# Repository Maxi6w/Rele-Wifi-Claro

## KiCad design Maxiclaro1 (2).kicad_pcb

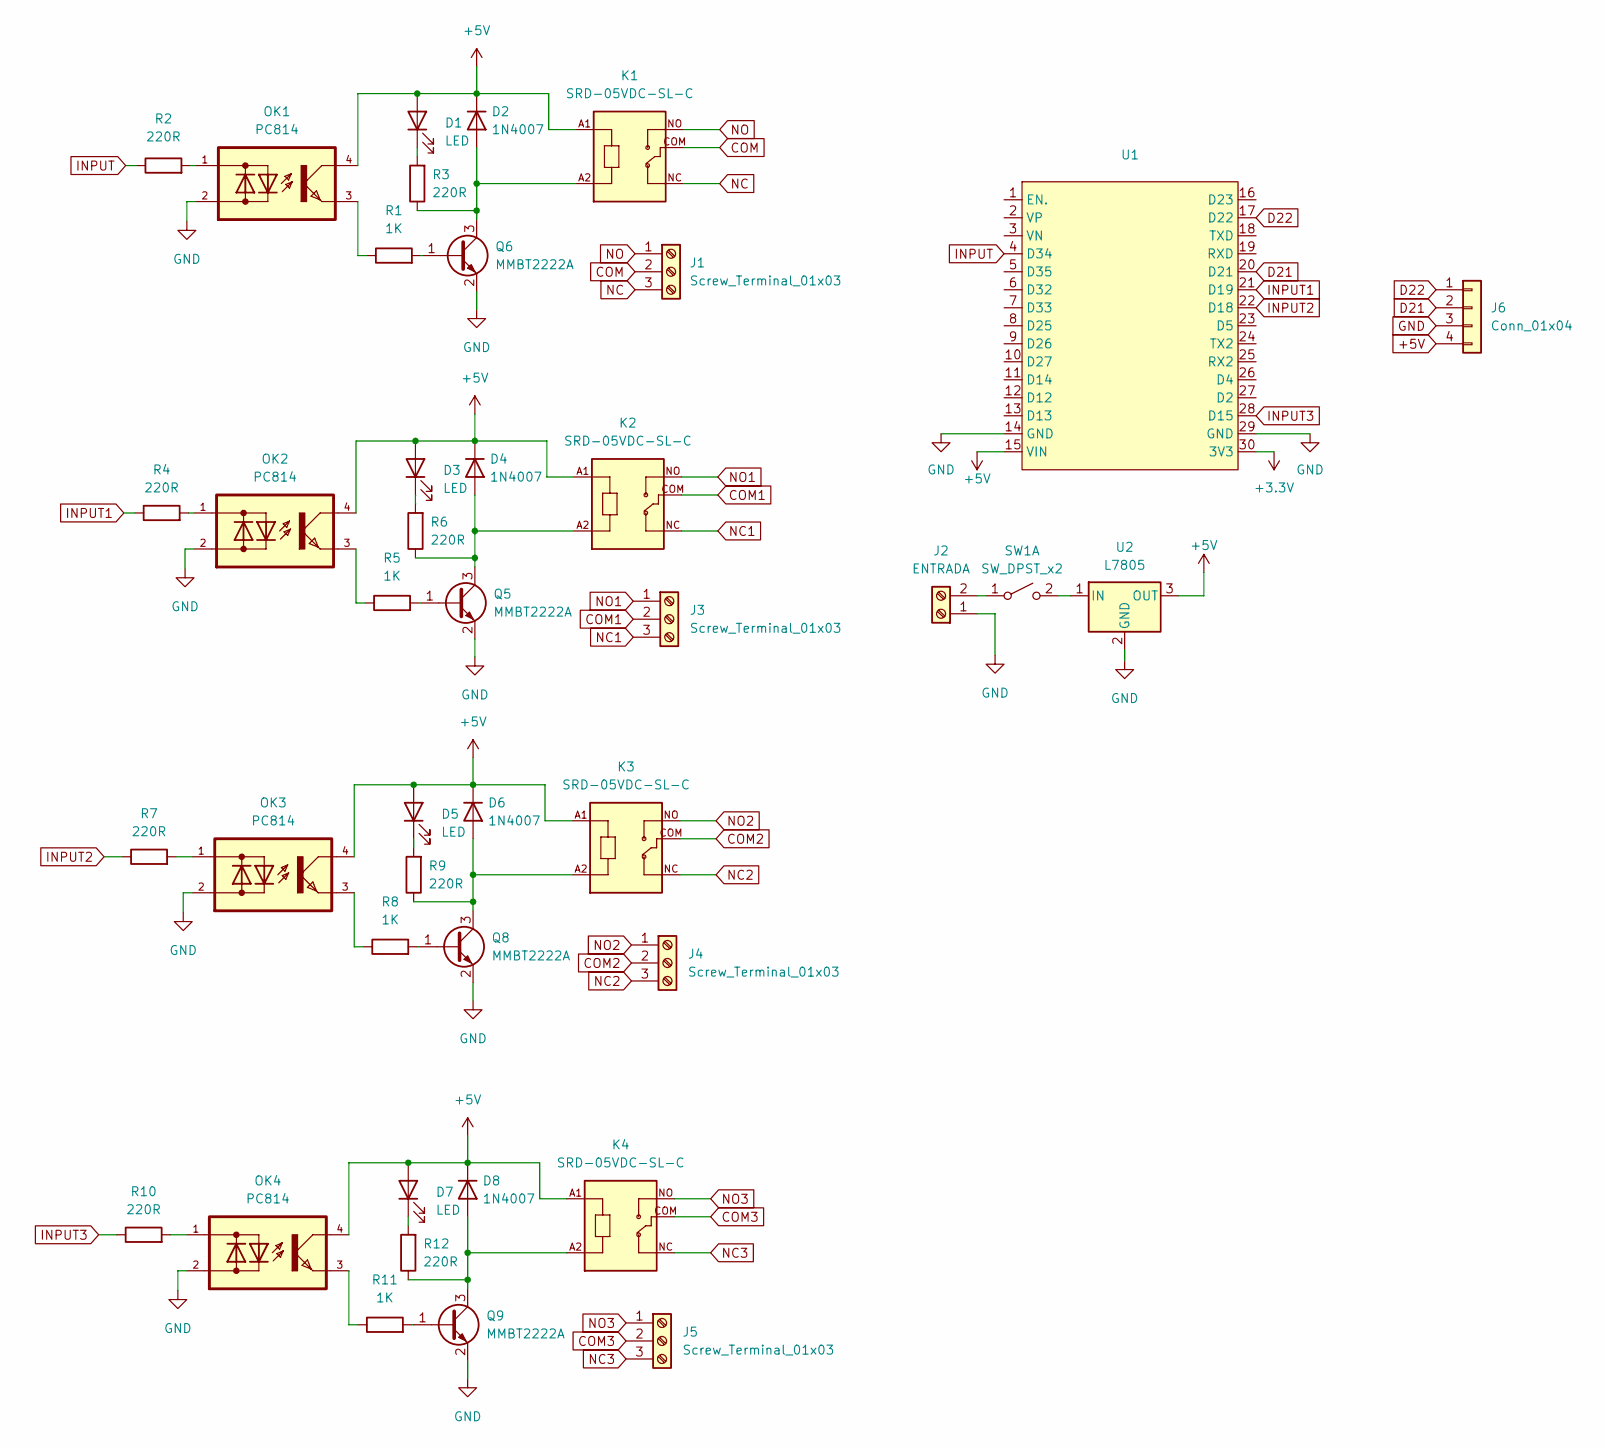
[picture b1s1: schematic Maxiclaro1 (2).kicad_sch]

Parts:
D1, D3, D5, D7: LED; LED_0805_2012Metric
D2, D4, D6, D8: 1N4007; D_0805_2012Metric
J1, J3, J4, J5: Screw_Terminal_01x03; TerminalBlock_bornier-3_P5.08mm
J2: ENTRADA; TerminalBlock_Altech_AK300-2_P5.00mm
J6: Conn_01x04; PinHeader_1x04_P2.54mm_Vertical
K1, K2, K3, K4: SRD-05VDC-SL-C; RELAY_SRD-05VDC-SL-C
OK1, OK2, OK3, OK4: PC814; DIL04
Q5, Q6, Q8, Q9: MMBT2222A; SOT-23
R1, R5, R8, R11: 1K; R_0805_2012Metric
R2, R3, R4, R6, R7, R9, R10, R12: 220R; R_0805_2012Metric
SW1: SW_DPST_x2; SW_2MS1T1B1M2QES-5
U1: ESP32_DevKit_V1_CH9102X
U2: L7805; TO-263-2

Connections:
+3.3V: U1.30 (3V3)
+5V: D1.2 (A), D2.1 (K), D3.2 (A), D4.1 (K), D5.2 (A), D6.1 (K), D7.2 (A), D8.1 (K), J6.4, K1.A1, K2.A1, K3.A1, K4.A1, OK1.4, OK2.4, OK3.4, OK4.4, U1.15 (VIN), U2.3 (OUT)
COM: J1.2, K1.COM
COM1: J3.2, K2.COM
COM2: J4.2, K3.COM
COM3: J5.2, K4.COM
D21: J6.2, U1.20 (D21)
D22: J6.1, U1.17 (D22)
GND: J2.1, J6.3, OK1.2, OK2.2, OK3.2, OK4.2, Q5.2 (E), Q6.2 (E), Q8.2 (E), Q9.2 (E), U1.14 (GND), U1.29 (GND), U2.2 (GND)
INPUT: R2.1, U1.4 (D34)
INPUT1: R4.1, U1.21 (D19)
INPUT2: R7.1, U1.22 (D18)
INPUT3: R10.1, U1.28 (D15)
NC: J1.3, K1.NC
NC1: J3.3, K2.NC
NC2: J4.3, K3.NC
NC3: J5.3, K4.NC
NO: J1.1, K1.NO
NO1: J3.1, K2.NO
NO2: J4.1, K3.NO
NO3: J5.1, K4.NO
unnamed: D1.1 (K), R3.2
unnamed: D2.2 (A), K1.A2, Q6.3 (C), R3.1
unnamed: D3.1 (K), R6.2
unnamed: D4.2 (A), K2.A2, Q5.3 (C), R6.1
unnamed: D5.1 (K), R9.2
unnamed: D6.2 (A), K3.A2, Q8.3 (C), R9.1
unnamed: D7.1 (K), R12.2
unnamed: D8.2 (A), K4.A2, Q9.3 (C), R12.1
unnamed: J2.2, SW1.1 (A)
unnamed: OK1.1, R2.2
unnamed: OK1.3, R1.1
unnamed: OK2.1, R4.2
unnamed: OK2.3, R5.1
unnamed: OK3.1, R7.2
unnamed: OK3.3, R8.1
unnamed: OK4.1, R10.2
unnamed: OK4.3, R11.1
unnamed: Q5.1 (B), R5.2
unnamed: Q6.1 (B), R1.2
unnamed: Q8.1 (B), R8.2
unnamed: Q9.1 (B), R11.2
unnamed: SW1.2 (B), U2.1 (IN)

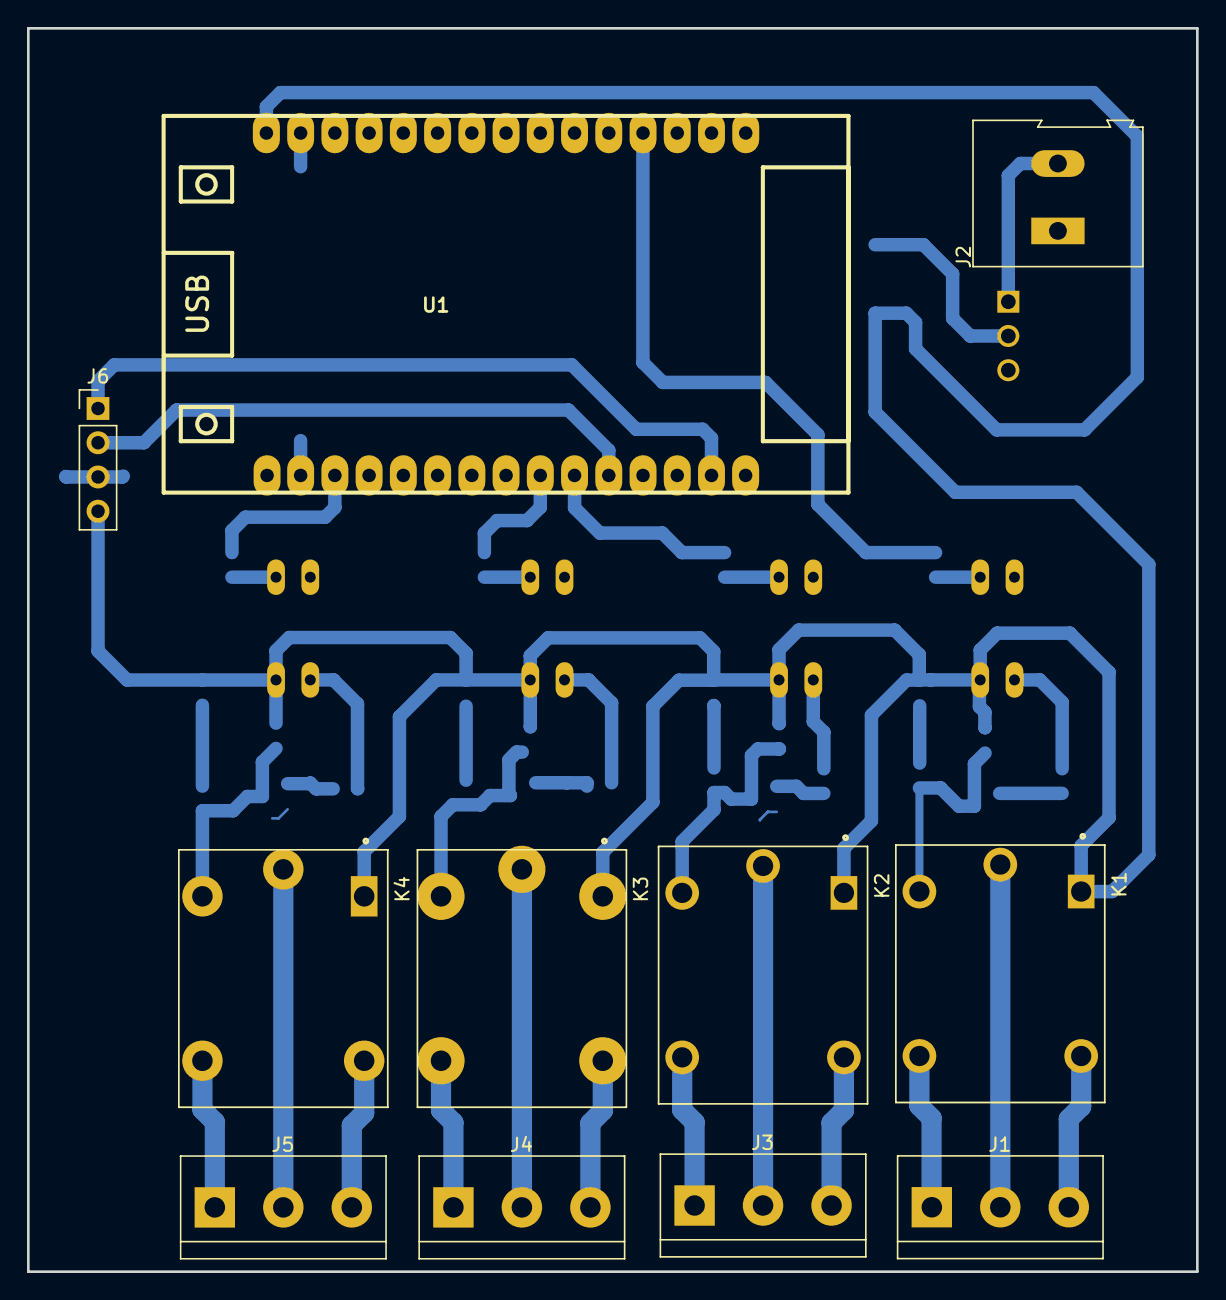
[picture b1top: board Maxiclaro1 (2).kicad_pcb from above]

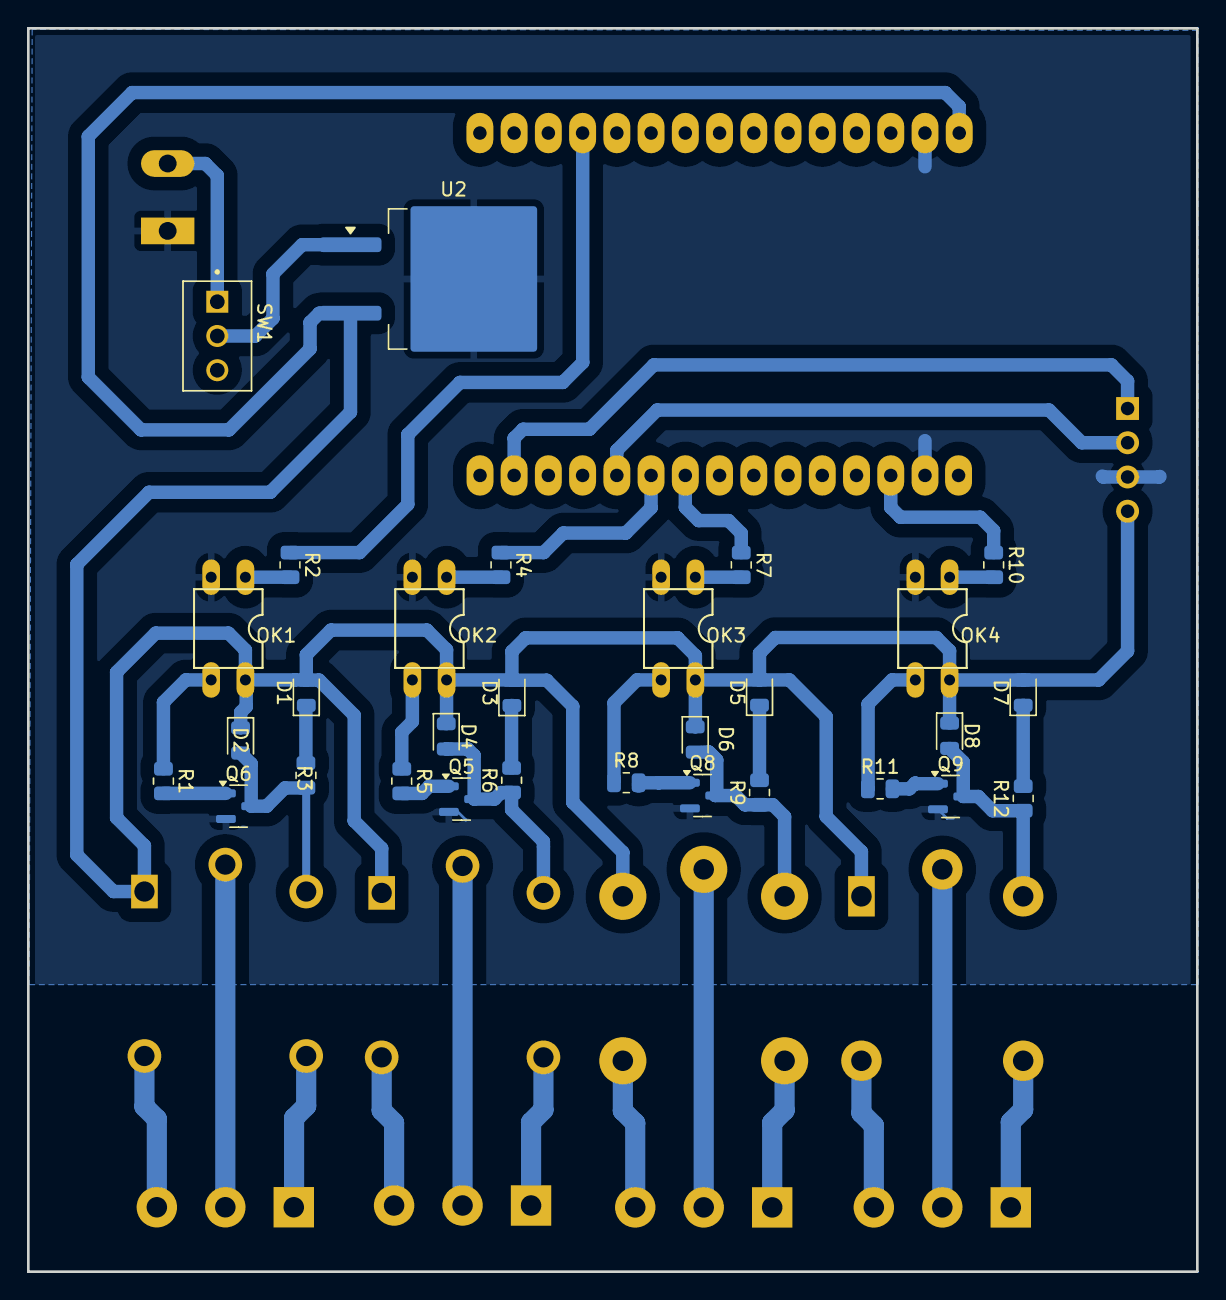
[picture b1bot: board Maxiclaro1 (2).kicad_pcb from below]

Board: 2 copper layers, 86.7 x 92.2 mm, 41 parts (30 on the bottom side), 42 nets.

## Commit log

2025-05-07 Mi primer commit
2025-06-11 1.0
    casi terminado bhdvdevdbcefsfrebjfvbhgv
